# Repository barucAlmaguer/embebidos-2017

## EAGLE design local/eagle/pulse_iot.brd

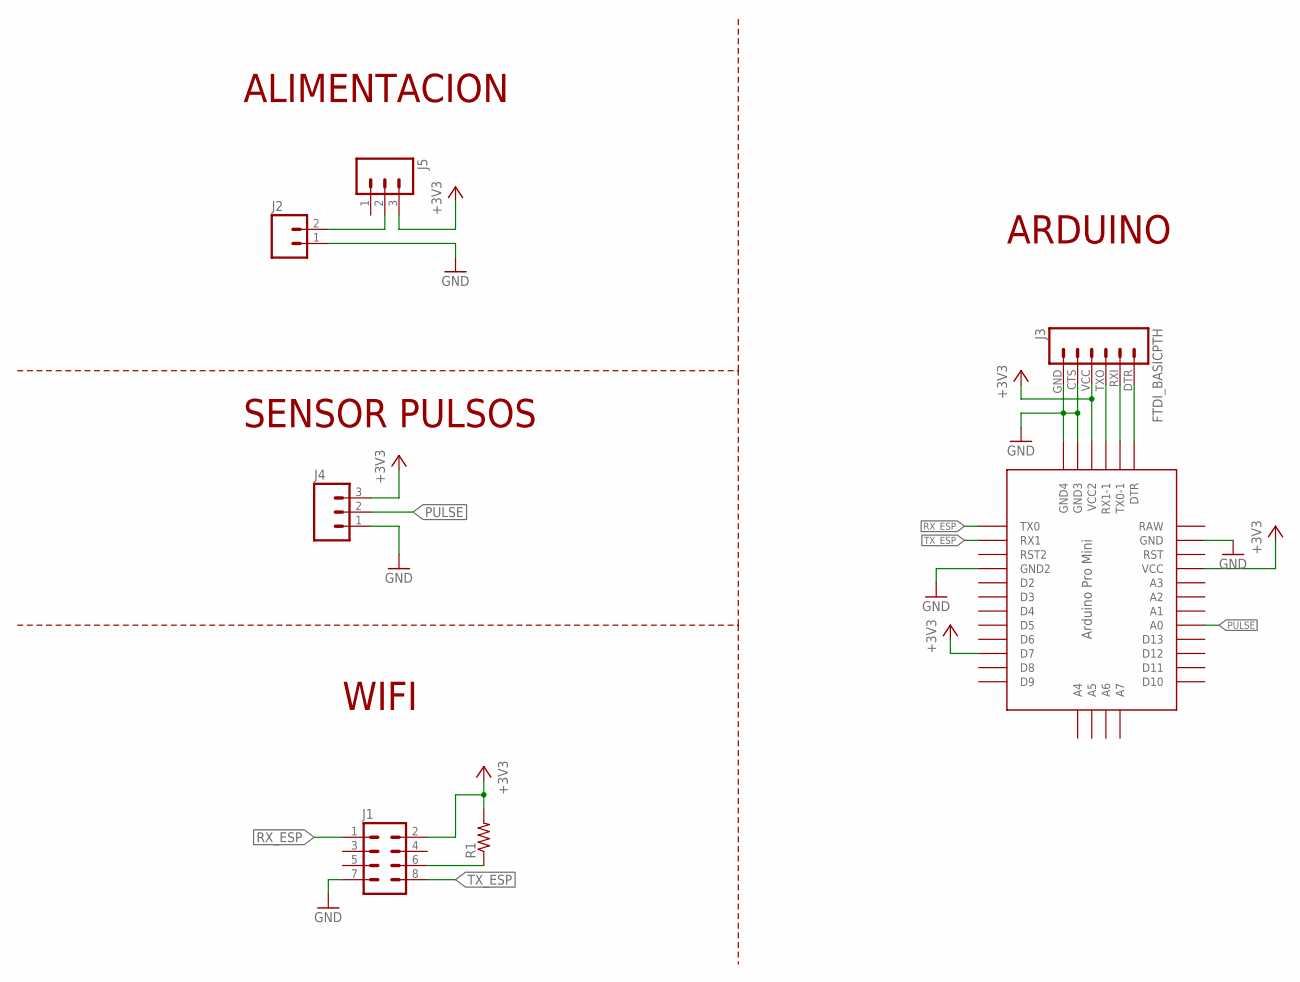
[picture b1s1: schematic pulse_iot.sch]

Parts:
J1: M04X2; 2X4
J2: M025MM; SCREWTERMINAL-5MM-2
J3: FTDI_BASICPTH; FTDI_BASIC
J4: M03-SCREW-5MM; SCREWTERMINAL-5MM-3
J5: M03LONGPADS; 1X03_LONGPADS
R1: RESISTORPTH1; AXIAL-0.3
U$1: PRO-MINI

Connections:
+3V3: J1.2, J3.VCC (4), J4.3, J5.3, R1.P$2 (2), U$1.D7, U$1.VCC, U$1.VCC1 (VCC2)
GND: J1.7, J2.1, J3.CTS (5), J3.GND (6), J4.1, U$1.GND, U$1.GND1 (GND2), U$1.GND2 (GND4), U$1.GND3
unnamed: J3.TXO (3), U$1.RX1-1
unnamed: J3.RXI (2), U$1.TX0-1
unnamed: J3.DTR (1), U$1.DTR
unnamed: J1.6, R1.P$1 (1)
unnamed: J2.2, J5.2
PULSE: J4.2, U$1.A0
RAW: U$1.RAW
RX_ESP: J1.1, U$1.TX0
TX_ESP: J1.8, U$1.RX1

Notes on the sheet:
WIFI
SENSOR PULSOS
ALIMENTACION
ARDUINO

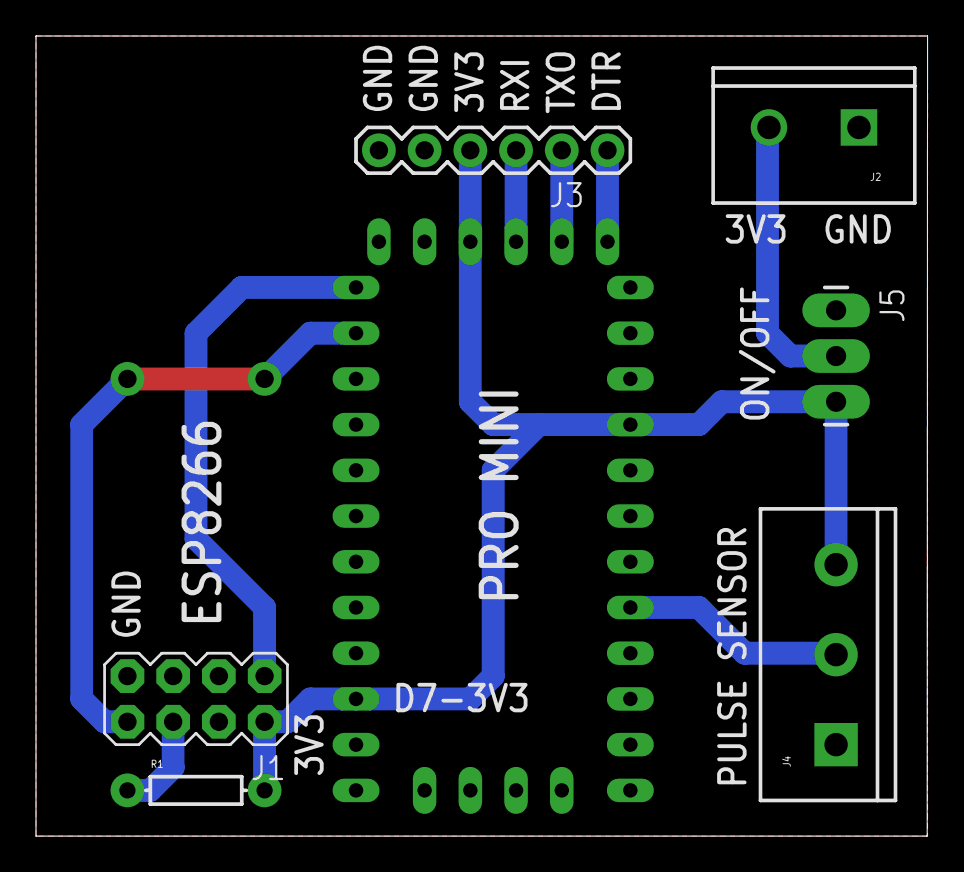
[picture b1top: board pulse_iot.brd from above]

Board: 2 copper layers, 49.5 x 44.5 mm, 7 parts (0 on the bottom side), 10 nets.

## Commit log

2017-11-08 commit inicial
2017-11-08 anadido logging simple
2017-11-08 bugs
2017-11-08 ignorando archivillos
2017-11-08 api de dato random
2017-11-08 aplastando bugs ;;;
2017-11-08 aplastando bugs ;;;;;;
2017-11-08 vista de tabla
2017-11-08 vista de tabla 2
2017-11-08 vista de tabla 3
2017-11-10 modificada pagina principal (mundo cruel)
2017-11-10 jsonificando
2017-11-27 ejemplo chart html + js
2017-11-27 mod de ruta de static js
2017-11-27 modificada ruta de chart y otras cosillas
2017-11-27 cambio de grafica de barras a grafica normalita
2017-11-27 obtenidos datos de grafica de BD real
2017-11-27 modificada escala de grafica
2017-11-27 jugando con estilos
2017-11-27 redirect log to home
2017-11-27 adaptacion de rango de chart
2017-11-27 redirect a home al postear un dato
2017-11-27 refactor y refresh cada 10 segundos
2017-11-29 prueba lagrange y movs carpetas para entrega
2017-11-29 weight.html
2017-11-29 posteo de peso
2017-11-29 asdf json
2017-11-29 ignoring mime type
2017-11-29 mimetype y espacio
2017-11-29 Agregada vista de datos Json y recepcion de datos en flask
2017-11-29 print de json en logs
2017-11-30 guardando en BD datos de JSON (tabla scale)

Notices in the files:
parts and their libraries:
SparkFun-Connectors: Licensing: Creative Commons ShareAlike 4.0 International - https://creativecommons.org/licenses/by-sa/4.0
SparkFun: Licensing: CC v3.0 Share-Alike You are welcome to use this library for commercial purposes.
